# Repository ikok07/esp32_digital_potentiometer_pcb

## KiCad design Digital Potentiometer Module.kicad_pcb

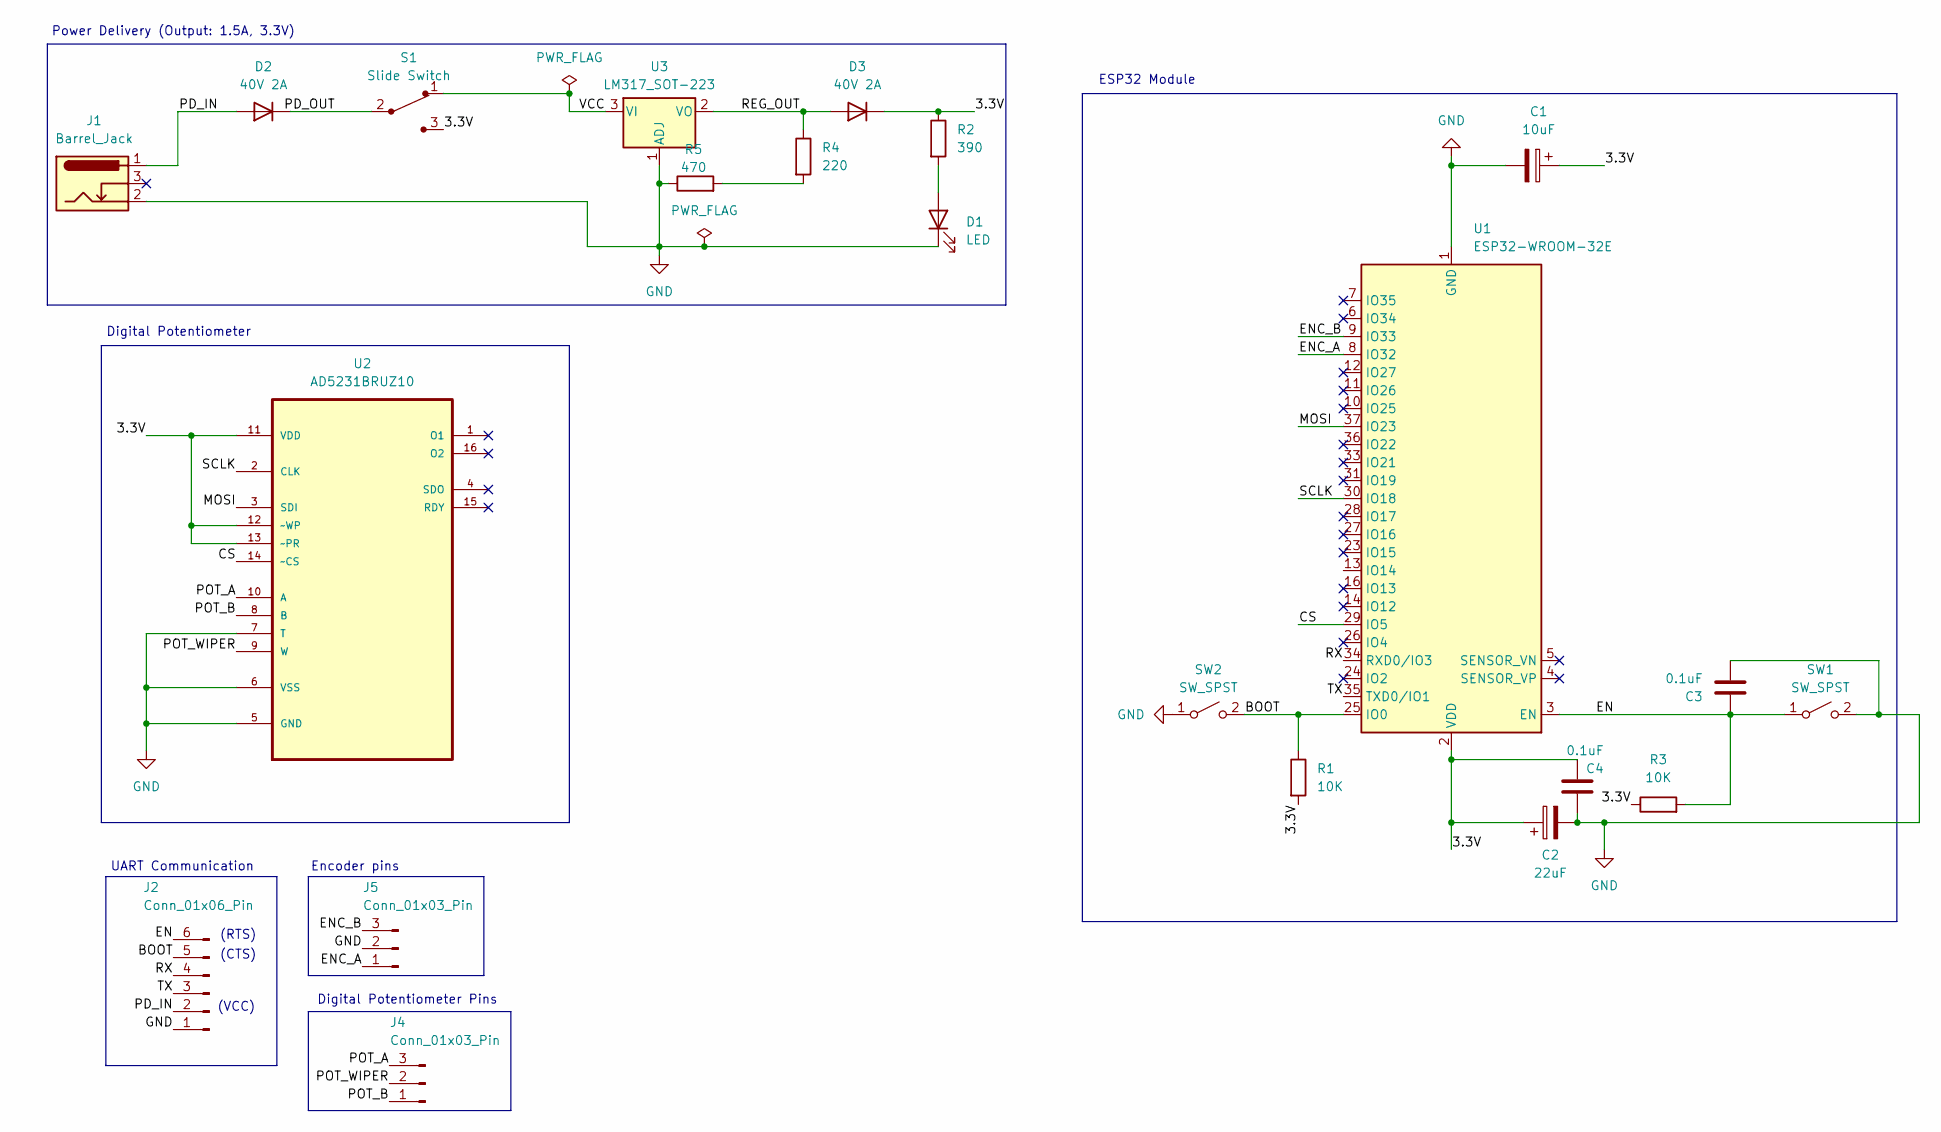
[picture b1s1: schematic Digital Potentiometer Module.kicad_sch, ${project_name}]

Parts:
C1: 10uF; CP_Elec_5x5.3
C2: 22uF; CP_Elec_5x5.3
C3, C4: 0.1uF; C_1206_3216Metric
D1: LED; LED_D3.0mm
D2, D3: 40V 2A; SK55-DO214AA
J1: Barrel_Jack; BarrelJack_Wuerth_6941xx301002
J2: Conn_01x06_Pin; PinHeader_1x06_P2.54mm_Vertical
J4, J5: Conn_01x03_Pin; PinHeader_1x03_P2.54mm_Vertical
R1, R3: 10K; R_0805_2012Metric_Pad1.20x1.40mm_HandSolder
R2: 390; R_0805_2012Metric_Pad1.20x1.40mm_HandSolder
R4: 220; R_0805_2012Metric_Pad1.20x1.40mm_HandSolder
R5: 470; R_0805_2012Metric_Pad1.20x1.40mm_HandSolder
S1: Slide Switch; PinHeader_1x03_P2.54mm_Vertical; MPN EG1218; Digi-Key_PN EG1903-ND
SW1, SW2: SW_SPST; SW_SPST_PTS645
U1: ESP32-WROOM-32E; XCVR_ESP32-WROOM-32E__4MB_
U2: AD5231BRUZ10; SOP65P640X120-16N; MPN AD5231BRUZ10
U3: LM317_SOT-223; SOT-223-3_TabPin2

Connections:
/3.3V: C1.1, C2.1, C4.1, D3.1 (K), R1.2, R2.1, R3.1, S1.3, U1.2 (VDD), U2.11 (VDD), U2.12 (~WP), U2.13 (~PR)
/BOOT: J2.5, R1.1, SW2.2 (B), U1.25 (IO0)
/CS: U1.29 (IO5), U2.14 (~CS)
/EN: C3.2, J2.6, R3.2, SW1.1 (A), U1.3 (EN)
/ENC_A: J5.1, U1.8 (IO32)
/ENC_B: J5.3, U1.9 (IO33)
/MOSI: U1.37 (IO23), U2.3 (SDI)
/PD_IN: D2.2 (A), J1.1, J2.2
/PD_OUT: D2.1 (K), S1.2
/POT_A: J4.3, U2.10 (A)
/POT_B: J4.1, U2.8 (B)
/POT_WIPER: J4.2, U2.9 (W)
/REG_OUT: D3.2 (A), R4.1, U3.2 (VO)
/RX: J2.4, U1.34 (RXD0/IO3)
/SCLK: U1.30 (IO18), U2.2 (CLK)
/TX: J2.3, U1.35 (TXD0/IO1)
/VCC: S1.1, U3.3 (VI)
GND: C1.2, C2.2, C3.1, C4.2, D1.1 (K), J1.2, J2.1, J5.2, R5.1, SW1.2 (B), SW2.1 (A), U1.1 (GND), U1.15 (GND), U1.38 (GND), U1.39 (GND), U2.5 (GND), U2.6 (VSS), U2.7 (T), U3.1 (ADJ)
unnamed: D1.2 (A), R2.2
unnamed: R4.2, R5.2

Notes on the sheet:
ESP32 Module
(RTS)
Digital Potentiometer
Power Delivery (Output: 1.5A, 3.3V)
(CTS)
UART Communication
(VCC)
Encoder pins
Digital Potentiometer Pins

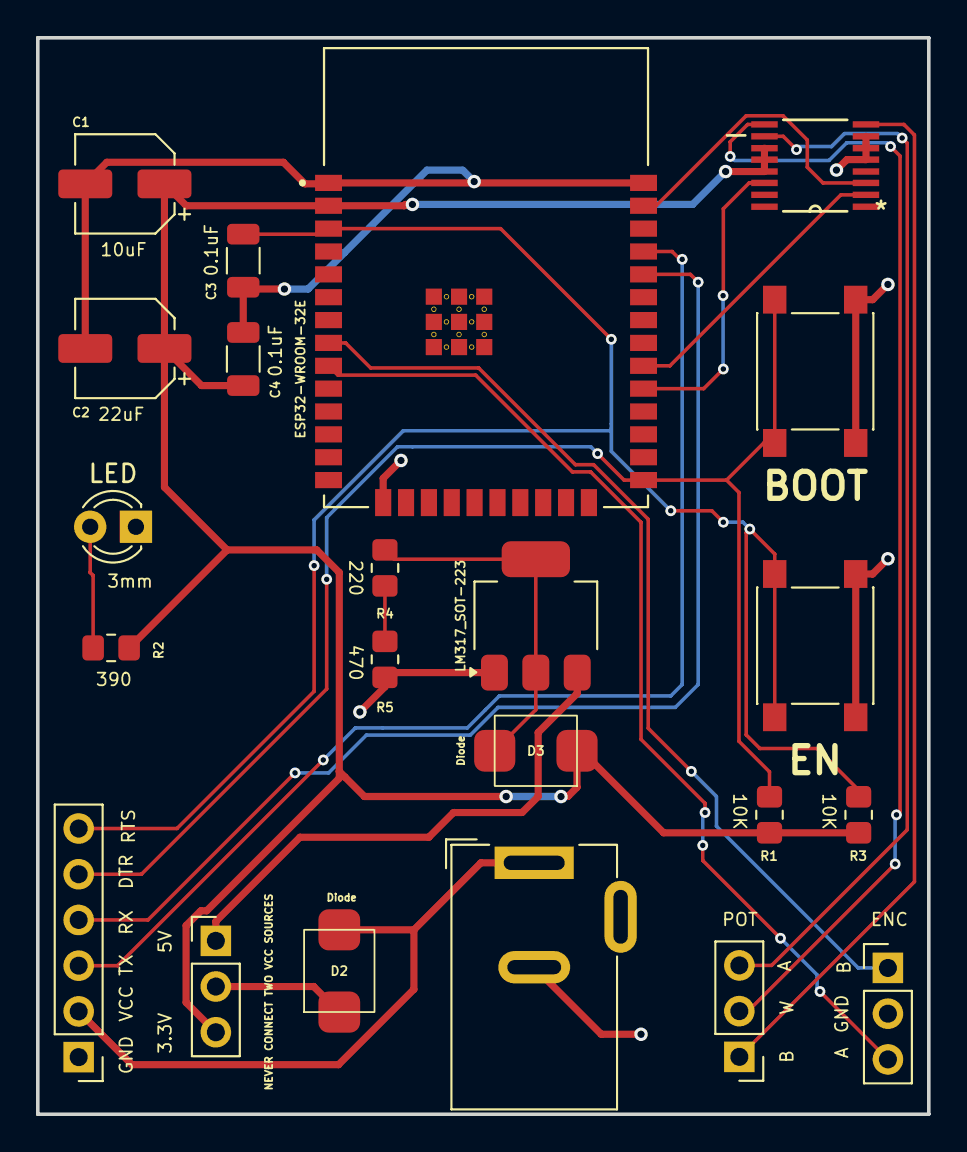
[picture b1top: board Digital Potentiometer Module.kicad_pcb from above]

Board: 2 copper layers, 49.5 x 59.8 mm, 22 parts (0 on the bottom side), 20 nets.

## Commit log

2024-09-23 design first schematic
2024-09-24 add footprints
2024-09-24 design pcb
2024-09-24 make improvements to pcb
2024-09-25 fix design issues
2024-09-25 fix bugs with pcb design
2024-09-25 fix UART communication pins
2024-09-26 add vcc, gnd pins. change dtr pin to cts
2024-09-28 fix issues with serial communication pins
2024-10-04 improve pcb design
